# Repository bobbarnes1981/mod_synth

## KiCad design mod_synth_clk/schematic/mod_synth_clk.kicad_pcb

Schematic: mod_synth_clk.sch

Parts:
A1: Arduino_Nano_v3.x; Arduino_Nano
D1: 1N4148; D_DO-35_SOD27_P7.62mm_Horizontal
D2: LED; LED_D5.0mm
J1: Clock; Jack_3.5mm_QingPu_WQP-PJ398SM_Vertical_CircularHoles
J2: Conn_02x08_Odd_Even; IDC-Header_2x08_P2.54mm_Vertical
R1, R2: 1k; R_Axial_DIN0207_L6.3mm_D2.5mm_P10.16mm_Horizontal
RV1: 100k Lin; Potentiometer_Alpha_RD901F-40-00D_Single_Vertical
RV2: 100k Lin; Potentiometer_Alpha_RD901F-40-00D_Single_Vertical_CircularH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

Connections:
+5V: A1.27 (+5V), J2.11, J2.12, RV1.3, RV2.3
GND: A1.29 (GND), D2.1 (K), J1.S, J2.4, J2.6, J2.8, RV1.1, RV2.1
unnamed: A1.16 (D13), D1.2 (A), R2.2
unnamed: A1.19 (A0), RV1.2
unnamed: A1.20 (A1), RV2.2
unnamed: D1.1 (K), R1.1
unnamed: D2.2 (A), R2.1
unnamed: J1.T, R1.2
unnamed: J2.3, J2.5, J2.7

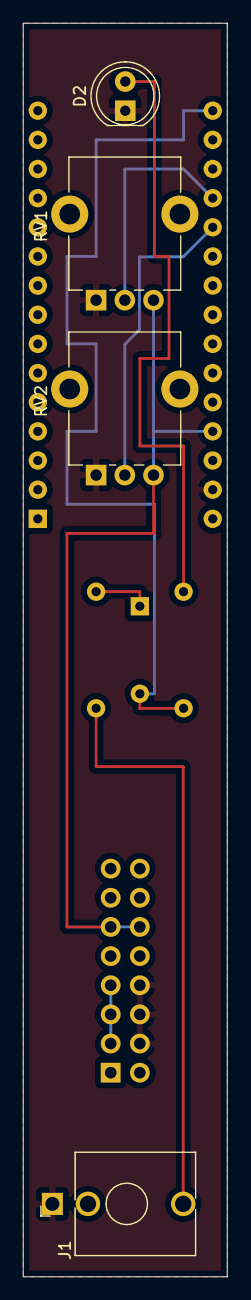
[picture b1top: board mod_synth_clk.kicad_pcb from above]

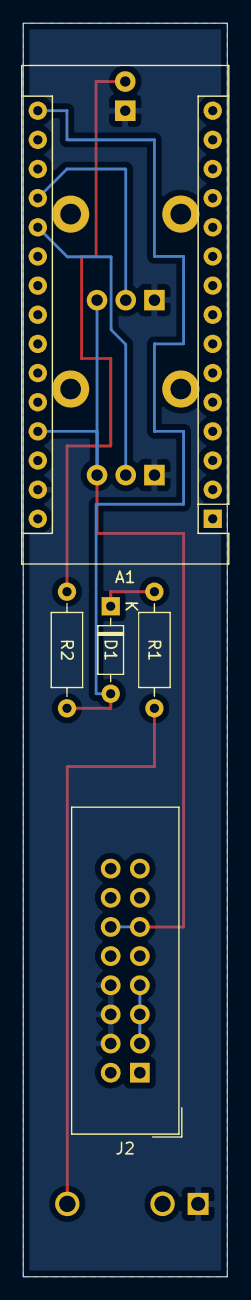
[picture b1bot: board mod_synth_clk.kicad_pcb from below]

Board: 2 copper layers, 17.8 x 109.2 mm, 9 parts (5 on the bottom side), 9 nets.

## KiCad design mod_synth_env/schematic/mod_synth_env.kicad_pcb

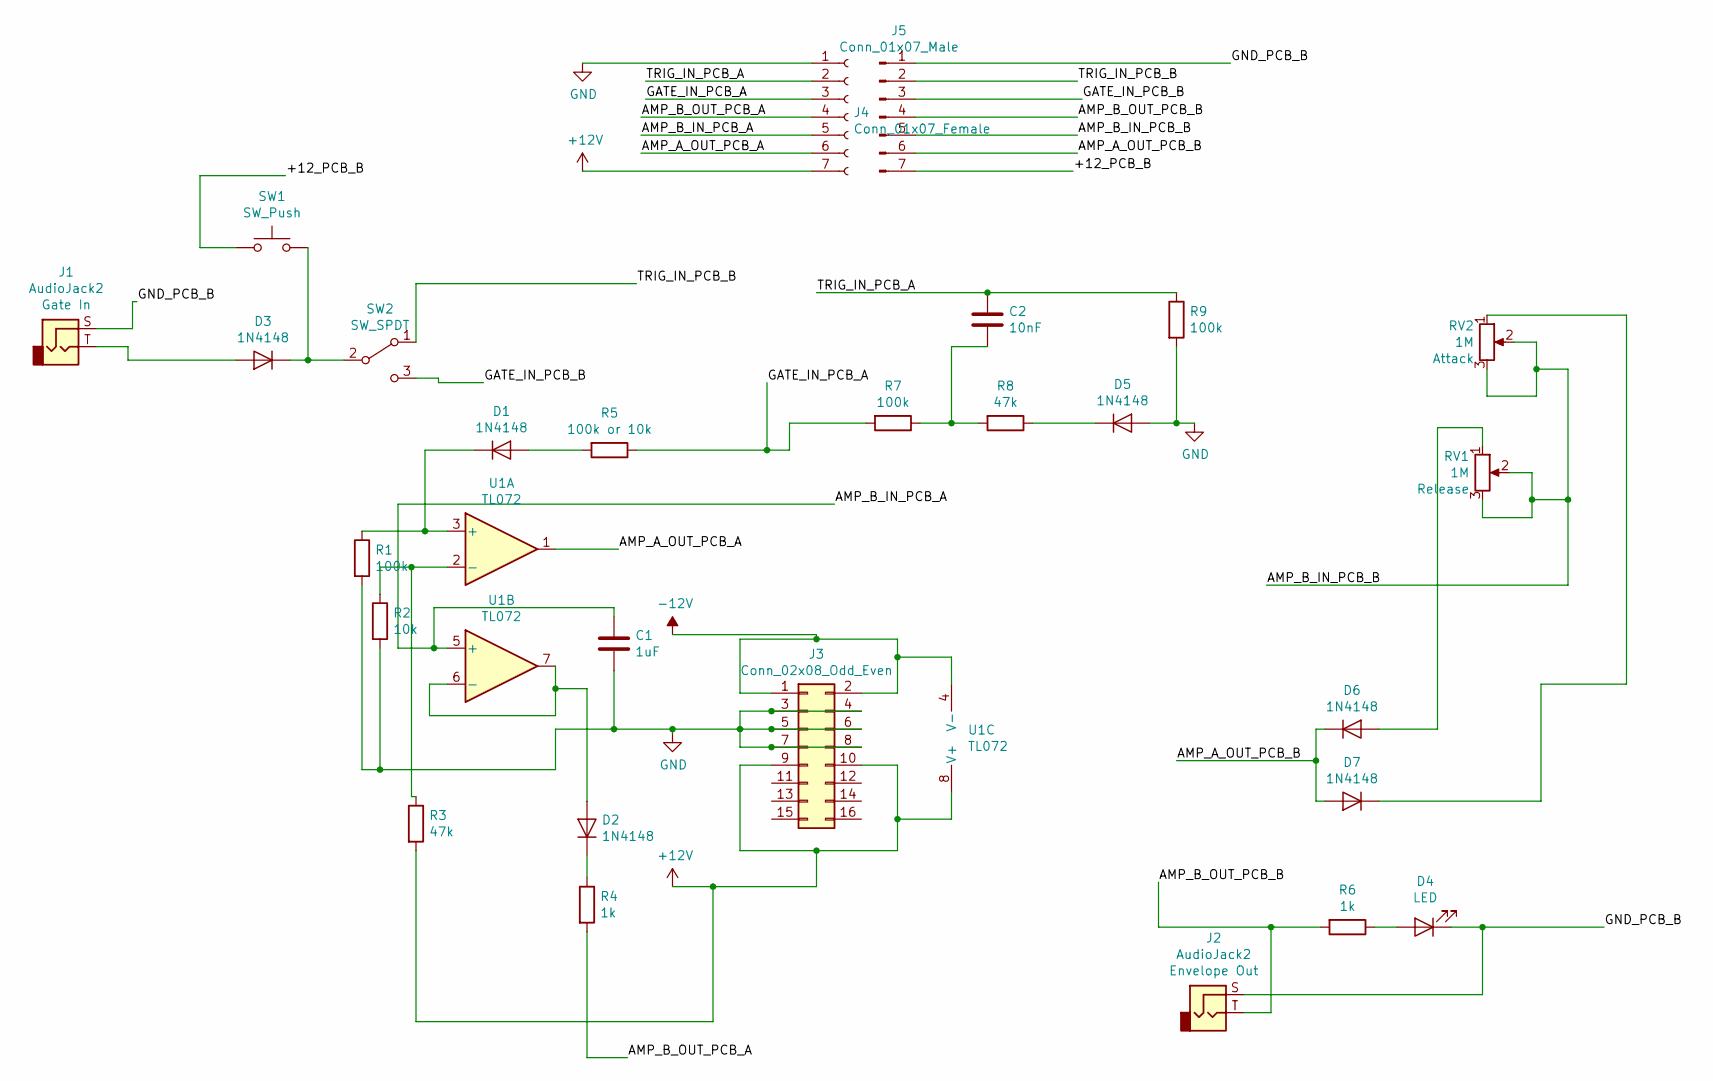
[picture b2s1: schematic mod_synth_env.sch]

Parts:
C1: 1uF; C_Disc_D9.0mm_W2.5mm_P5.00mm
C2: 10nF; C_Disc_D9.0mm_W2.5mm_P5.00mm
D1, D2, D3, D5, D6, D7: 1N4148; D_DO-35_SOD27_P7.62mm_Horizontal
D4: LED; LED_D5.0mm
J1, J2: AudioJack2; Jack_3.5mm_QingPu_WQP-PJ398SM_Vertical_CircularHoles
J3: Conn_02x08_Odd_Even; IDC-Header_2x08_P2.54mm_Vertical
J4: Conn_01x07_Female; PinSocket_1x07_P2.54mm_Vertical
J5: Conn_01x07_Male; PinHeader_1x07_P2.54mm_Vertical
R1, R7, R9: 100k; R_Axial_DIN0207_L6.3mm_D2.5mm_P10.16mm_Horizontal
R2: 10k; R_Axial_DIN0207_L6.3mm_D2.5mm_P10.16mm_Horizontal
R3, R8: 47k; R_Axial_DIN0207_L6.3mm_D2.5mm_P10.16mm_Horizontal
R4, R6: 1k; R_Axial_DIN0207_L6.3mm_D2.5mm_P10.16mm_Horizontal
R5: 100k or 10k; R_Axial_DIN0207_L6.3mm_D2.5mm_P10.16mm_Horizontal
RV1, RV2: 1M; Potentiometer_Alpha_RD901F-40-00D_Single_Vertical_CircularH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
SW1: SW_Push; PinHeader_1x02_P2.54mm_Vertical
SW2: SW_SPDT; SPDT_Switch_Vertical
U1: TL072; DIP-8_W7.62mm_Socket_LongPads

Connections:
+12V: J3.9, J3.10, J4.7, R3.2, U1.8 (V+)
-12V: J3.1, J3.2, U1.4 (V-)
/+12_PCB_B: J5.7, SW1.1
/AMP_A_OUT_PCB_A: J4.6, U1.1
/AMP_A_OUT_PCB_B: D6.1 (K), D7.2 (A), J5.6
/AMP_B_IN_PCB_A: C1.1, J4.5, U1.5 (+)
/AMP_B_IN_PCB_B: J5.5, RV1.2, RV1.3, RV2.2, RV2.3
/AMP_B_OUT_PCB_A: J4.4, R4.2
/AMP_B_OUT_PCB_B: J2.T, J5.4, R6.2
/GATE_IN_PCB_A: J4.3, R5.1, R7.2
/GATE_IN_PCB_B: J5.3, SW2.3 (C)
/GND_PCB_B: D4.1 (K), J1.S, J2.S, J5.1
/TRIG_IN_PCB_A: C2.1, J4.2, R9.1
/TRIG_IN_PCB_B: J5.2, SW2.1 (A)
GND: C1.2, D5.2 (A), J3.3, J3.4, J3.5, J3.6, J3.7, J3.8, J4.1, R1.2, R2.2, R9.2
unnamed: C2.2, R7.1, R8.2
unnamed: D1.1 (K), R1.1, U1.3 (+)
unnamed: D1.2 (A), R5.2
unnamed: D2.1 (K), R4.1
unnamed: D2.2 (A), U1.6 (-), U1.7
unnamed: D3.1 (K), SW1.2, SW2.2 (B)
unnamed: D3.2 (A), J1.T
unnamed: D4.2 (A), R6.1
unnamed: D5.1 (K), R8.1
unnamed: D6.2 (A), RV1.1
unnamed: D7.1 (K), RV2.1
unnamed: R2.1, R3.1, U1.2 (-)

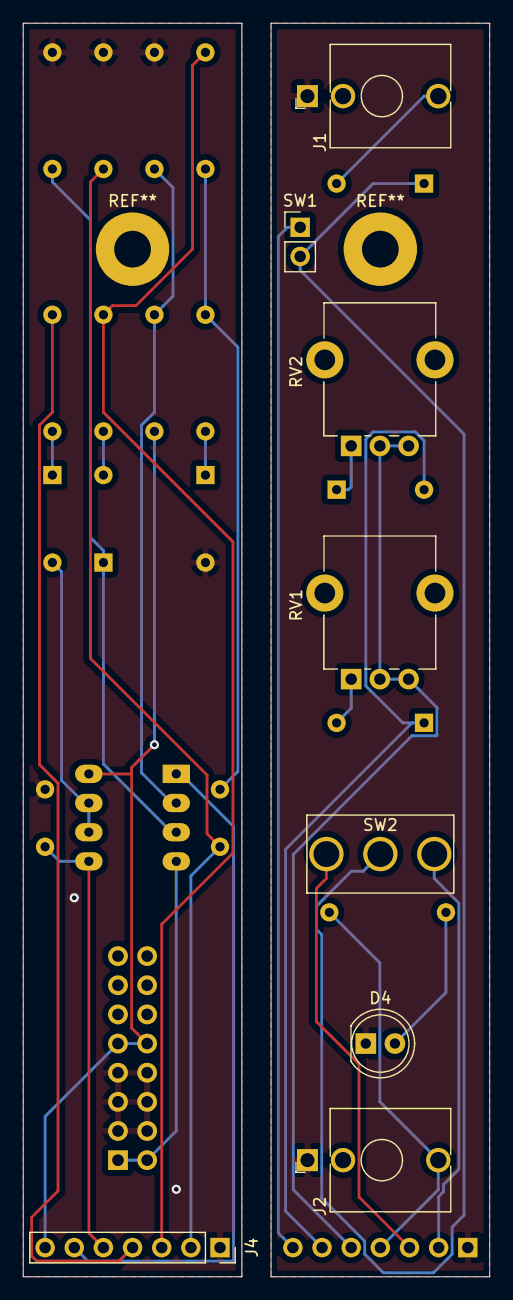
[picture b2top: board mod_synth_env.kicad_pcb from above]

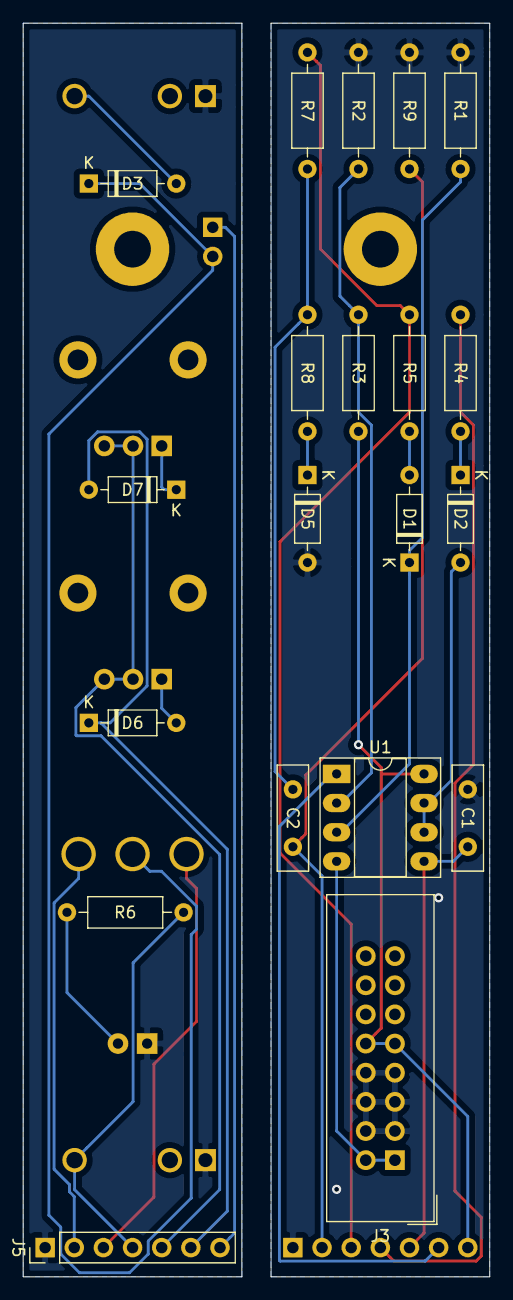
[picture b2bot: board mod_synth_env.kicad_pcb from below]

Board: 2 copper layers, 40.6 x 109.2 mm, 28 parts (20 on the bottom side), 27 nets.

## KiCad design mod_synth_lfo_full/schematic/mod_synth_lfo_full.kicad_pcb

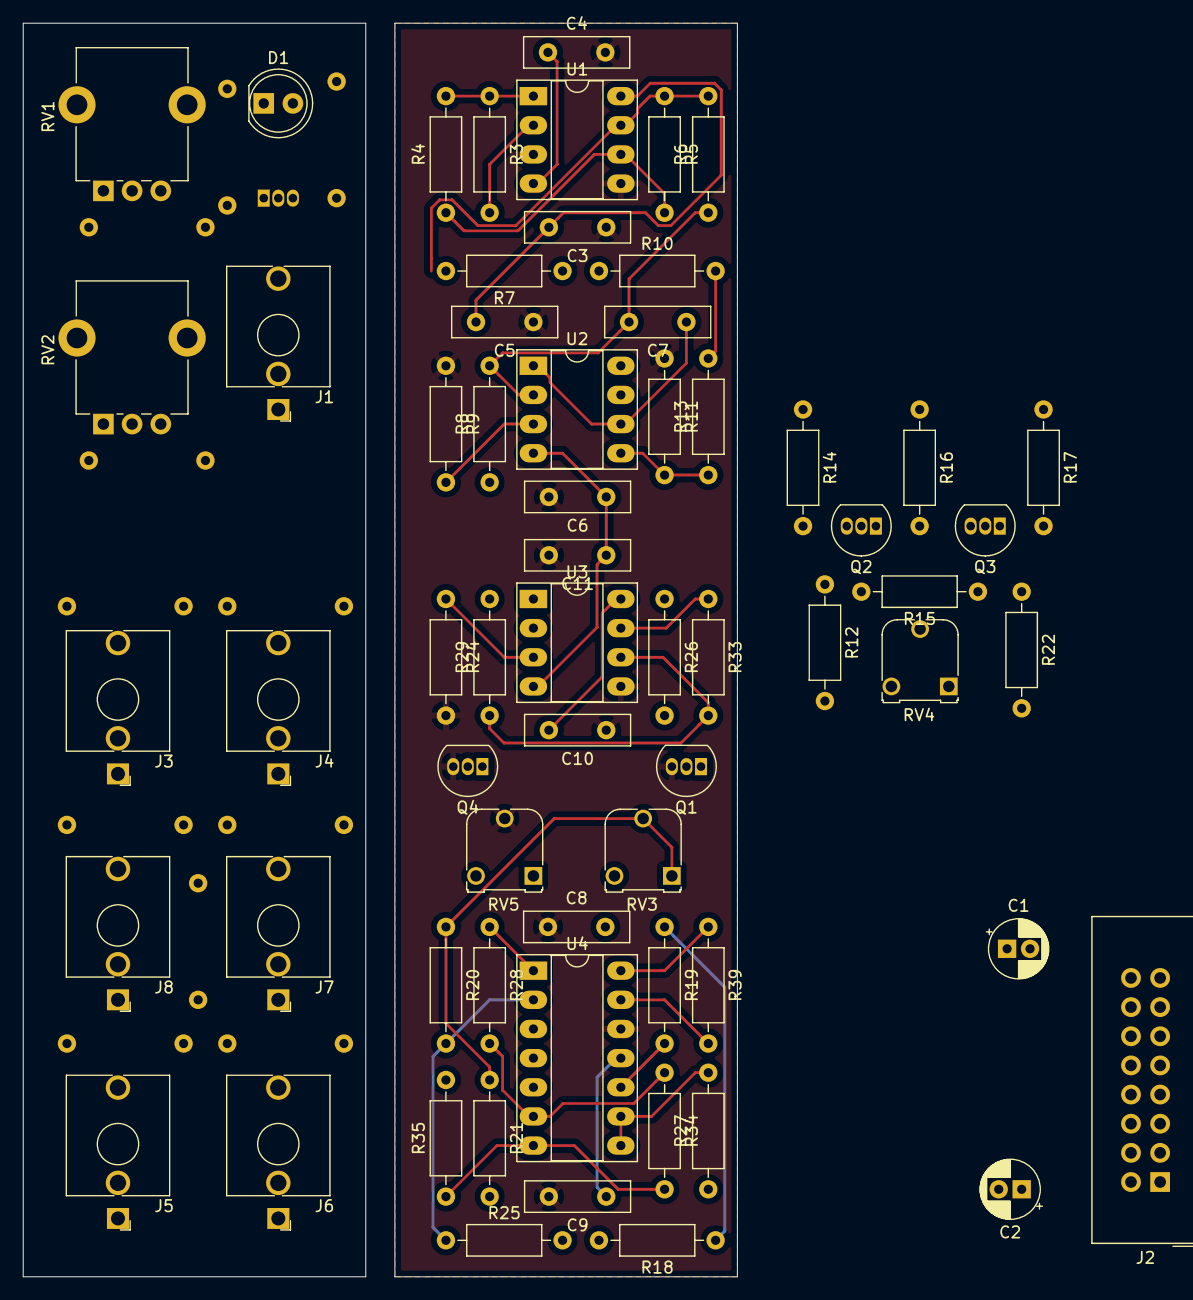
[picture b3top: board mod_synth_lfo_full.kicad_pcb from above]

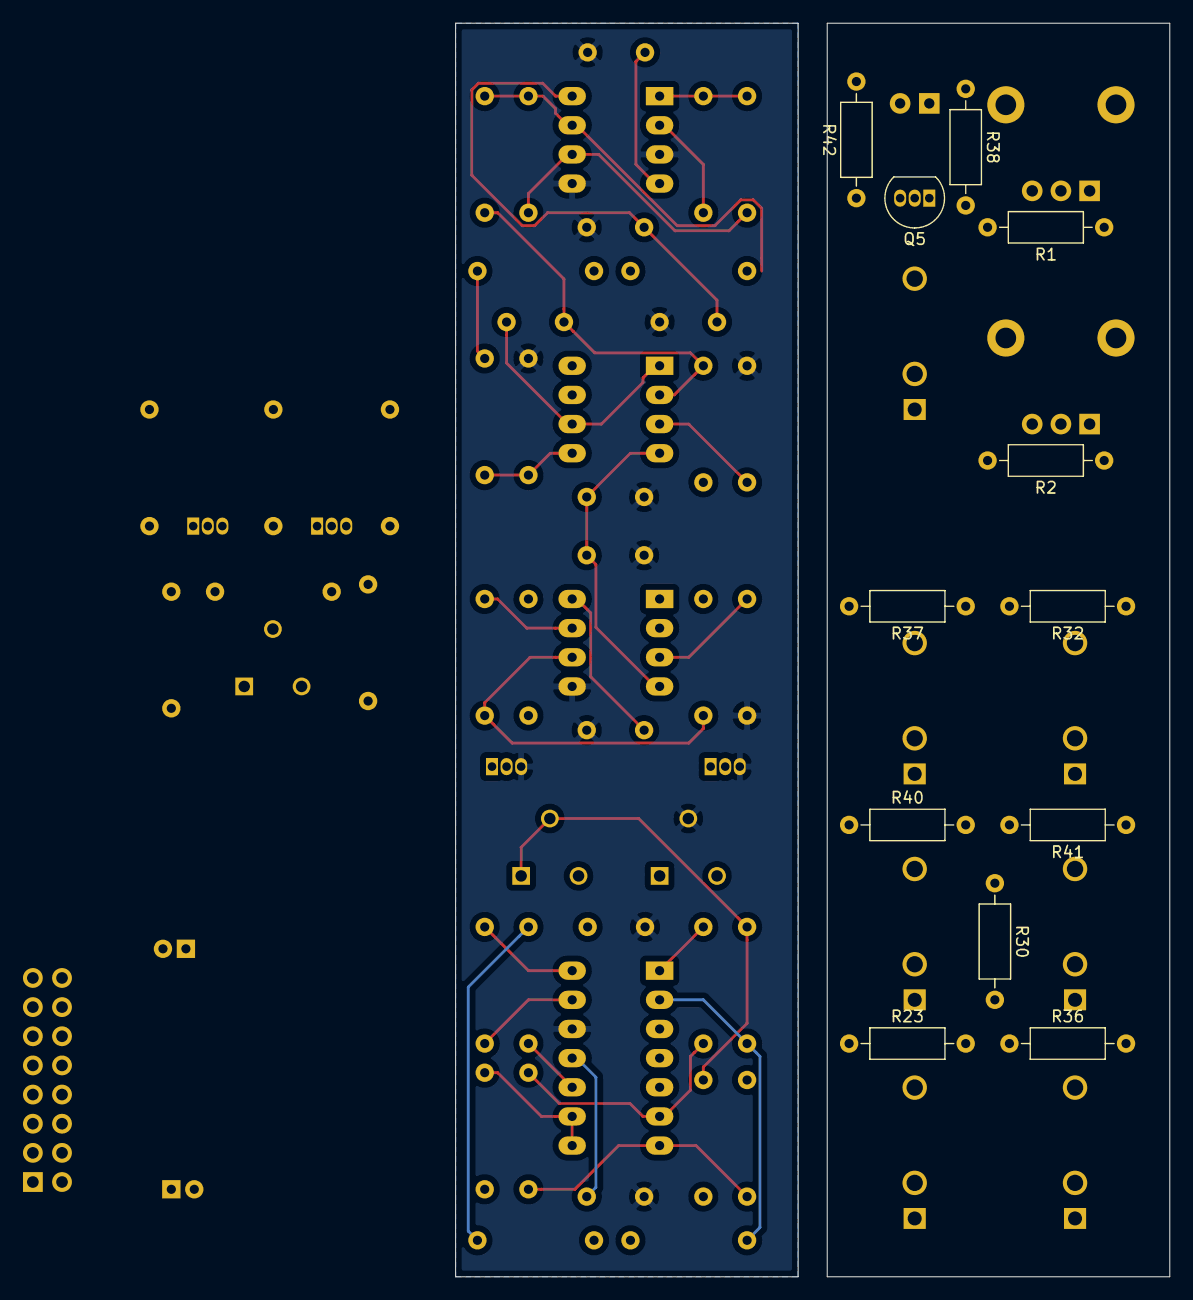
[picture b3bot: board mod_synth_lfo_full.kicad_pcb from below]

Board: 2 copper layers, 62.2 x 109.2 mm, 75 parts (12 on the bottom side), 47 nets.

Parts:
C1, C2: 10uf; CP_Radial_D5.0mm_P2.00mm
C3, C4, C5, C6, C7, C8, C9, C10, C11: 100nf; C_Disc_D9.0mm_W2.5mm_P5.00mm
D1: LED; LED_D5.0mm
J1: CV; Jack_3.5mm_QingPu_WQP-PJ398SM_Vertical_CircularHoles
J2: Conn_02x08_Odd_Even; IDC-Header_2x08_P2.54mm_Vertical
J3: SIN; Jack_3.5mm_QingPu_WQP-PJ398SM_Vertical_CircularHoles
J4: COS; Jack_3.5mm_QingPu_WQP-PJ398SM_Vertical_CircularHoles
J5: TRI; Jack_3.5mm_QingPu_WQP-PJ398SM_Vertical_CircularHoles
J6: SQR; Jack_3.5mm_QingPu_WQP-PJ398SM_Vertical_CircularHoles
J7: RAMP UP; Jack_3.5mm_QingPu_WQP-PJ398SM_Vertical_CircularHoles
J8: RAMP DOWN; Jack_3.5mm_QingPu_WQP-PJ398SM_Vertical_CircularHoles
Q1, Q2, Q3, Q4, Q5: BC550; TO-92_Inline
R1, R2, R3, R4, R5, R6, R19, R20, R21, R23, R25, R30: 100k; R_Axial_DIN0207_L6.3mm_D2.5mm_P10.16mm_Horizontal
R7, R8, R9, R11, R13: 47k; R_Axial_DIN0207_L6.3mm_D2.5mm_P10.16mm_Horizontal
R10, R14, R17, R18, R29, R33, R34, R35, R38, R39: 10k; R_Axial_DIN0207_L6.3mm_D2.5mm_P10.16mm_Horizontal
R12, R22: 470; R_Axial_DIN0207_L6.3mm_D2.5mm_P10.16mm_Horizontal
R15: 220; R_Axial_DIN0207_L6.3mm_D2.5mm_P10.16mm_Horizontal
R16: 68k; R_Axial_DIN0207_L6.3mm_D2.5mm_P10.16mm_Horizontal
R24, R26: 33k; R_Axial_DIN0207_L6.3mm_D2.5mm_P10.16mm_Horizontal
R27: 50k; R_Axial_DIN0207_L6.3mm_D2.5mm_P10.16mm_Horizontal
R28: 20k; R_Axial_DIN0207_L6.3mm_D2.5mm_P10.16mm_Horizontal
R32, R36, R37, R40, R41, R42: 1k; R_Axial_DIN0207_L6.3mm_D2.5mm_P10.16mm_Horizontal
RV1: SPEED; Potentiometer_Alpha_RD901F-40-00D_Single_Vertical_CircularH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
RV2: CV AMOUNT; Potentiometer_Alpha_RD901F-40-00D_Single_Vertical_CircularH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
RV3: 100k; Potentiometer_Runtron_RM-065_Vertical
RV4: 50k; Potentiometer_Runtron_RM-065_Vertical
RV5: 20k; Potentiometer_Runtron_RM-065_Vertical
U1, U2, U3: TL072; DIP-8_W7.62mm_Socket_LongPads
U4: TL074; DIP-14_W7.62mm_Socket_LongPads

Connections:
+12V: C1.1, C3.2, C5.2, C8.2, C10.2, D1.2, J2.9, J2.10, R14.1, R17.1, RV1.1, U1.8, U2.8, U3.8, U4.4
-12V: C2.2, C4.1, C6.1, C9.1, C11.1, J2.1, J2.2, R16.1, U1.4, U2.4, U3.4, U4.11
GND: C1.2, C2.1, C3.1, C4.2, C5.1, C6.2, C8.1, C9.2, C10.1, C11.2, J1.S, J2.3, J2.4, J2.5, J2.6, J2.7, J2.8, J3.S, J4.S, J5.S, J6.S, J7.S, J8.S, Q1.3, Q4.3, R9.1, R11.1, R12.2, R22.2, R24.2, R30.2, R42.2, RV1.3, RV2.3, RV5.2, U1.3, U1.5, U3.5, U4.12
unnamed: C7.1, R20.1, R21.1, R36.1, R38.1, RV3.1, RV3.2, U2.1, U2.6
unnamed: C7.2, R6.1, R8.2, U2.2
unnamed: D1.1, Q5.1
unnamed: J1.T, RV2.1
unnamed: J3.T, R32.1
unnamed: J4.T, R37.1
unnamed: J5.T, R36.2
unnamed: J6.T, R23.2, R30.1
unnamed: J7.T, R40.2
unnamed: J8.T, R41.1
unnamed: Q1.1, R8.1
unnamed: Q1.2, R10.1
unnamed: Q2.1, R14.2, R26.2, U3.2
unnamed: Q2.2, R12.1, RV3.3
unnamed: Q2.3, R15.2, RV4.3
unnamed: Q3.1, R17.2, R24.1, U3.3
unnamed: Q3.2, R22.1
unnamed: Q3.3, R15.1, RV4.1
unnamed: Q4.1, R21.2, U4.3
unnamed: Q4.2, R18.2
unnamed: Q5.2, R38.2
unnamed: Q5.3, R42.1
unnamed: R1.1, R2.1, R3.2, U1.2
unnamed: R1.2, RV1.2
unnamed: R2.2, RV2.2
unnamed: R3.1, R4.2, U1.1
unnamed: R4.1, R5.2, U1.6
unnamed: R5.1, R6.2, R7.2, U1.7
unnamed: R7.1, R9.2, U2.3
unnamed: R10.2, R13.2, R18.1, R19.1, R23.1, U2.7
unnamed: R11.2, R13.1, U2.5
unnamed: R16.2, RV4.2
unnamed: R19.2, U4.10
unnamed: R20.2, R25.1, U4.2
unnamed: R25.2, R28.1, U4.1
unnamed: R26.1, R29.2, R32.2, U3.1
unnamed: R27.1, RV5.1, U4.5
unnamed: R27.2, U4.8, U4.9
unnamed: R28.2, R34.1, U4.6
unnamed: R29.1, R33.2, U3.6
unnamed: R33.1, R37.2, U3.7
unnamed: R34.2, R35.1, R40.1, U4.7
unnamed: R35.2, R39.2, U4.13
unnamed: R39.1, R41.2, U4.14

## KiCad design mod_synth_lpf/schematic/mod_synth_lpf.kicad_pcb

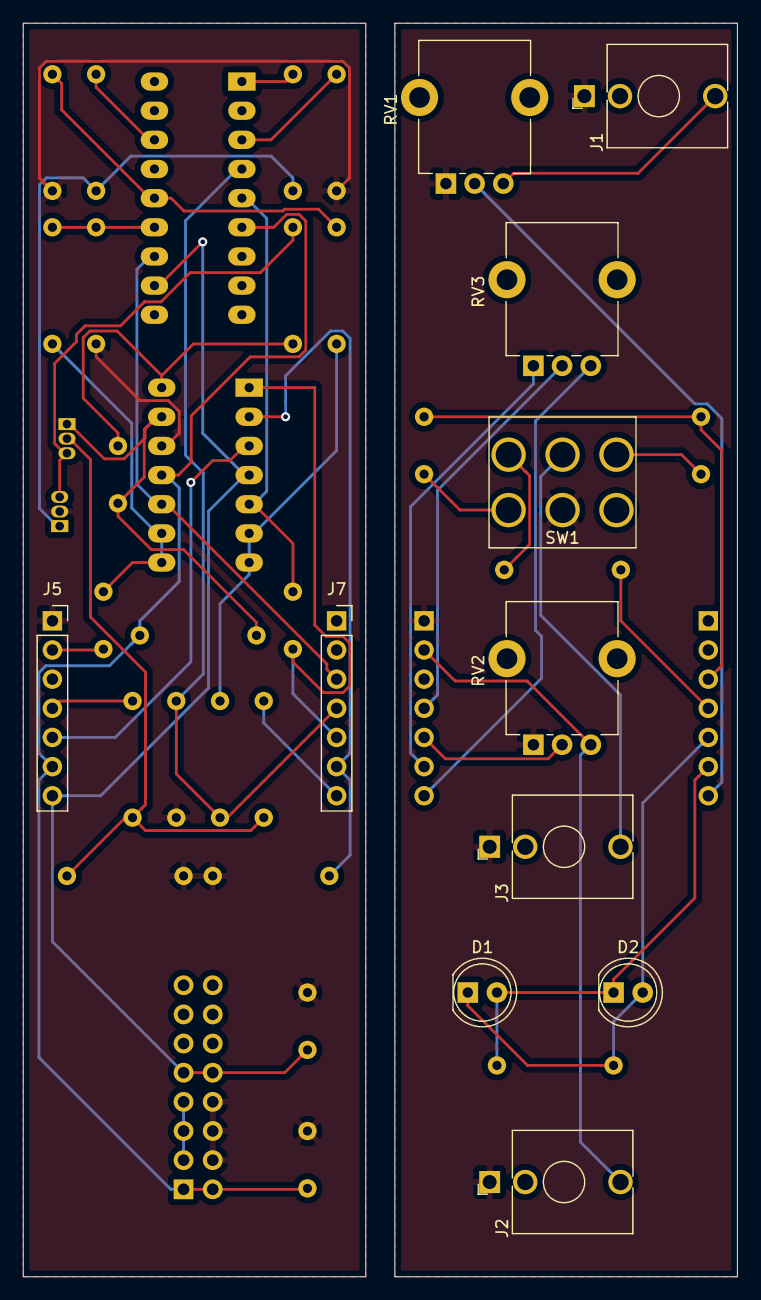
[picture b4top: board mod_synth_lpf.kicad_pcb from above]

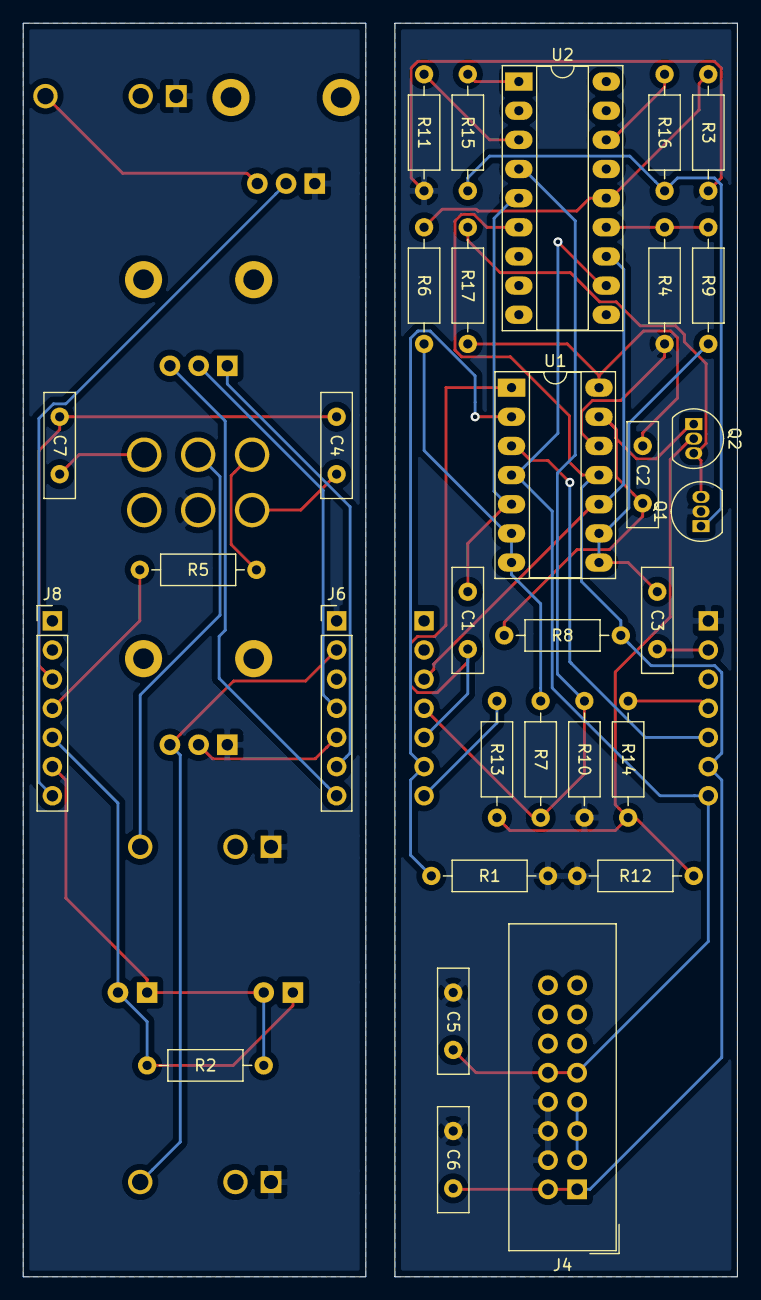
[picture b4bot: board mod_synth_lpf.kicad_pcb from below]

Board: 2 copper layers, 62.2 x 109.2 mm, 42 parts (31 on the bottom side), 41 nets.

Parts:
C1, C4, C7: 1nf; C_Disc_D9.0mm_W2.5mm_P5.00mm
C2: 4.7nf; C_Disc_D9.0mm_W2.5mm_P5.00mm
C3: 470nf; C_Disc_D9.0mm_W2.5mm_P5.00mm
C5, C6: 100nf; C_Disc_D9.0mm_W2.5mm_P5.00mm
D1, D2: LED; LED_D5.0mm
J1, J2, J3: AudioJack2; Jack_3.5mm_QingPu_WQP-PJ398SM_Vertical_CircularHoles
J4: Conn_02x08_Odd_Even; IDC-Header_2x08_P2.54mm_Vertical
J5, J7: Conn_01x07_Female; PinSocket_1x07_P2.54mm_Vertical
J6, J8: Conn_01x07_Male; PinHeader_1x07_P2.54mm_Vertical
Q1, Q2: BC558; TO-92_Inline
R1, R12: 1k8; R_Axial_DIN0207_L6.3mm_D2.5mm_P10.16mm_Horizontal
R2, R5, R6, R7, R9, R15, R16: 10k; R_Axial_DIN0207_L6.3mm_D2.5mm_P10.16mm_Horizontal
R3, R4, R10, R11: 220; R_Axial_DIN0207_L6.3mm_D2.5mm_P10.16mm_Horizontal
R8: 470k; R_Axial_DIN0207_L6.3mm_D2.5mm_P10.16mm_Horizontal
R13, R14: 100k; R_Axial_DIN0207_L6.3mm_D2.5mm_P10.16mm_Horizontal
R17: 4k7; R_Axial_DIN0207_L6.3mm_D2.5mm_P10.16mm_Horizontal
RV1, RV2: 100k Linear; Potentiometer_Alpha_RD901F-40-00D_Single_Vertical_CircularH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
RV3: 4.7k Linear; Potentiometer_Alpha_RD901F-40-00D_Single_Vertical_CircularH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
SW1: SW_DPDT_x2; DPDT_Switch_Vertical
U1: TL074; DIP-14_W7.62mm_Socket_LongPads
U2: LM13700; DIP-18_W7.62mm_Socket_LongPads

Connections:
+12V: C5.2, J4.9, J4.10, J5.7, U1.4, U2.11
-12V: C6.2, J4.1, J4.2, J5.6, R8.2, U1.11, U2.6
/+12_PCB_B: J6.7, RV3.3
/-12_PCB_B: J6.6, RV3.1
/AUDIO_OUT_PCB_A: C3.2, J5.2
/AUDIO_OUT_PCB_B: J2.T, J6.2, RV2.3
/CUT_OFF_PCB_A: J5.4, R14.2
/CUT_OFF_PCB_B: J6.4, RV3.2
/CV_PCB_A: J7.7, R13.1
/CV_PCB_B: J8.7, RV1.2
/GND_PCB_B: J1.S, J2.S, J3.S, J6.1, RV1.1, RV2.1, SW1.2
/INDICATOR_1_PCB_A: J7.6, R1.1, U1.2
/INDICATOR_1_PCB_B: D1.2, D2.1, J8.6, R2.2
/INDICATOR_2_PCB_A: C1.2, J7.5, U1.1
/INDICATOR_2_PCB_B: D1.1, D2.2, J8.5, R2.1
/RESONANCE_PCB_A: J5.5, U1.3
/RESONANCE_PCB_B: J6.5, RV2.2
/SWA_PCB_A: J7.3, U1.10, U2.12
/SWA_PCB_B: C4.1, C7.1, J8.3
/SWB_PCB_A: J7.4, R7.1, R10.1, U2.4
/SWB_PCB_B: J8.4, R5.1
GND: C5.1, C6.1, J4.4, J4.6, J4.8, J5.1, Q1.2, R1.2, R3.1, R4.1, R10.2, R11.2, R12.2, U1.12
unnamed: C1.1, U1.5, U2.5
unnamed: C2.1, R17.2, U1.14
unnamed: C2.2, Q2.1, R8.1, U1.13
unnamed: C3.1, R9.2, U1.8, U1.9
unnamed: C4.2, SW1.1
unnamed: C7.2, SW1.6
unnamed: J1.T, RV1.3
unnamed: J3.T, SW1.5
unnamed: J4.3, J4.5, J4.7
unnamed: Q1.1, R15.2, R16.1
unnamed: Q1.3, Q2.3, R17.1
unnamed: Q2.2, R12.1, R13.2, R14.1
unnamed: R3.2, R6.2, U2.14
unnamed: R4.2, R9.1, U2.13
unnamed: R5.2, SW1.4
unnamed: R6.1, R7.2, U1.6, U1.7
unnamed: R11.1, U2.3
unnamed: R15.1, U2.1
unnamed: R16.2, U2.16

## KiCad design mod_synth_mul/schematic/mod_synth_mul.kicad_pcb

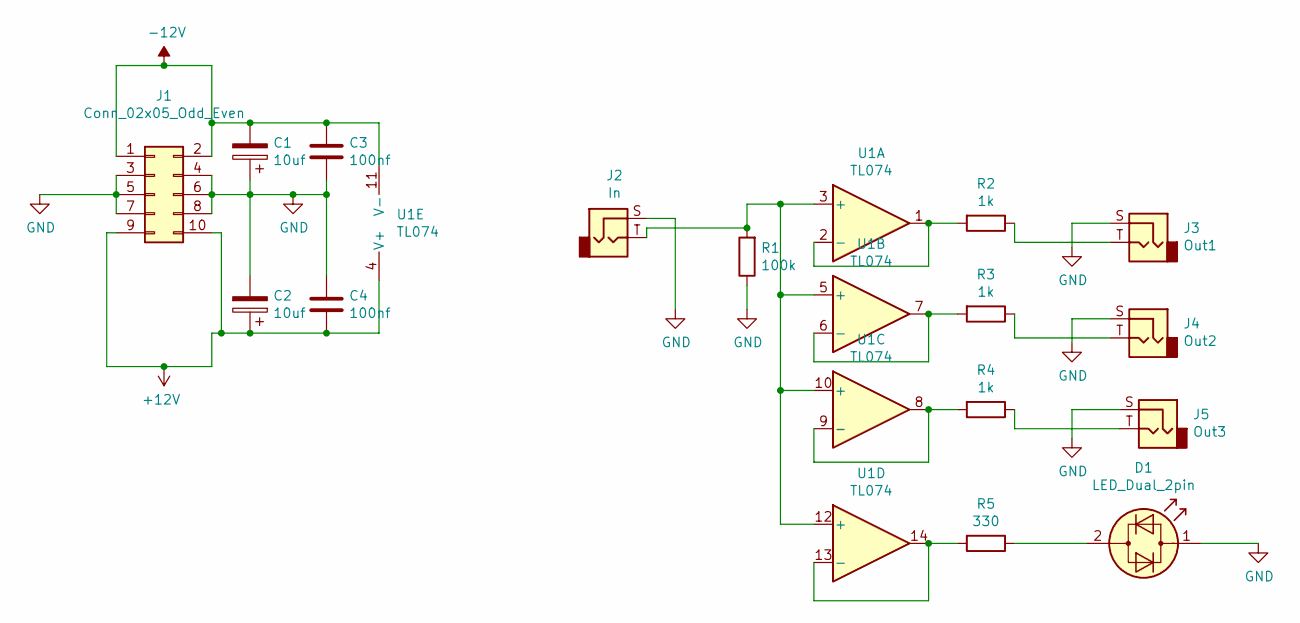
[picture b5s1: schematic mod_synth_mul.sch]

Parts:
C1, C2: 10uf; CP_Radial_D5.0mm_P2.00mm
C3, C4: 100nf; C_Disc_D9.0mm_W2.5mm_P5.00mm
D1: LED_Dual_2pin; LED_D5.0mm
J1: Conn_02x05_Odd_Even; IDC-Header_2x05_P2.54mm_Vertical
J2: In; Jack_3.5mm_QingPu_WQP-PJ398SM_Vertical_CircularHoles
J3: Out1; Jack_3.5mm_QingPu_WQP-PJ398SM_Vertical_CircularHoles
J4: Out2; Jack_3.5mm_QingPu_WQP-PJ398SM_Vertical_CircularHoles
J5: Out3; Jack_3.5mm_QingPu_WQP-PJ398SM_Vertical_CircularHoles
R1: 100k; R_Axial_DIN0207_L6.3mm_D2.5mm_P10.16mm_Horizontal
R2, R3, R4: 1k; R_Axial_DIN0207_L6.3mm_D2.5mm_P10.16mm_Horizontal
R5: 330; R_Axial_DIN0207_L6.3mm_D2.5mm_P10.16mm_Horizontal
U1: TL074; DIP-14_W7.62mm_Socket_LongPads

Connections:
+12V: C2.1, C4.2, J1.9, J1.10, U1.4 (V+)
-12V: C1.2, C3.1, J1.1, J1.2, U1.11 (V-)
GND: C1.1, C2.2, C3.2, C4.1, D1.1 (KA), J1.3, J1.4, J1.5, J1.6, J1.7, J1.8, J2.S, J3.S, J4.S, J5.S, R1.1
unnamed: D1.2 (AK), R5.1
unnamed: J2.T, R1.2, U1.3 (+), U1.5 (+), U1.10 (+), U1.12 (+)
unnamed: J3.T, R2.1
unnamed: J4.T, R3.1
unnamed: J5.T, R4.1
unnamed: R2.2, U1.1, U1.2 (-)
unnamed: R3.2, U1.6 (-), U1.7
unnamed: R4.2, U1.8, U1.9 (-)
unnamed: R5.2, U1.13 (-), U1.14

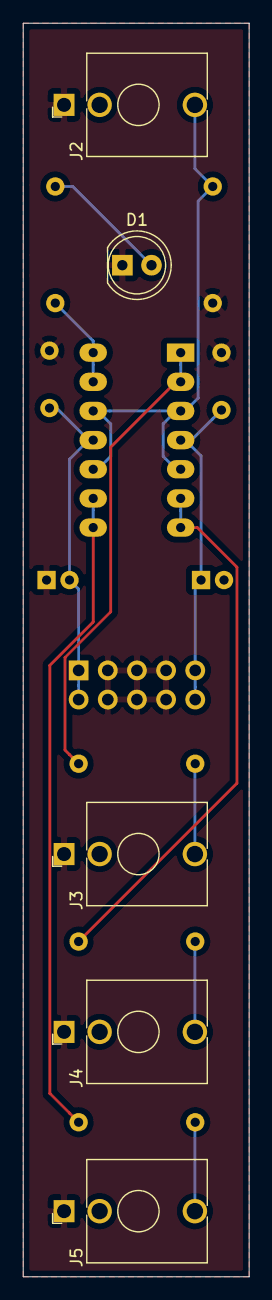
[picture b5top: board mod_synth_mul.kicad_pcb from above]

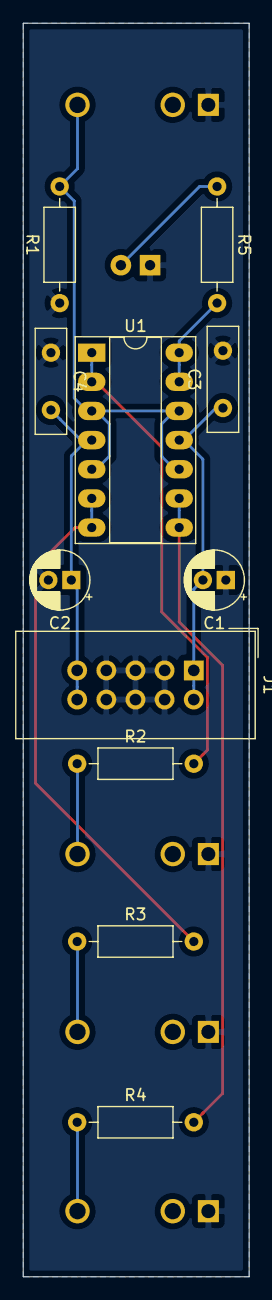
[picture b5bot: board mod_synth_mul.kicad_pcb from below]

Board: 2 copper layers, 19.7 x 109.2 mm, 16 parts (11 on the bottom side), 12 nets.

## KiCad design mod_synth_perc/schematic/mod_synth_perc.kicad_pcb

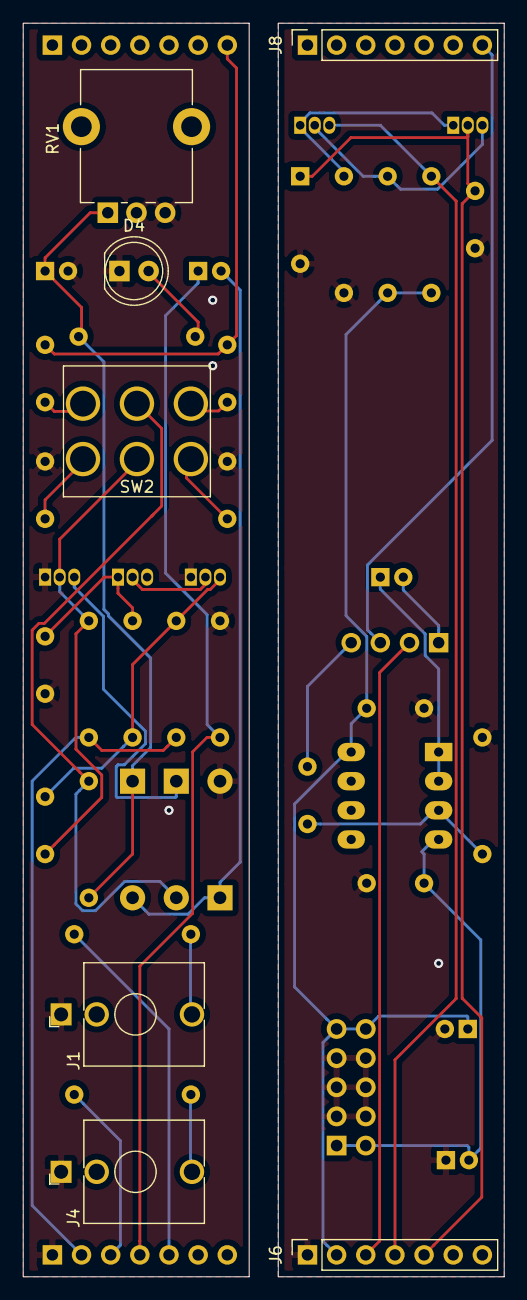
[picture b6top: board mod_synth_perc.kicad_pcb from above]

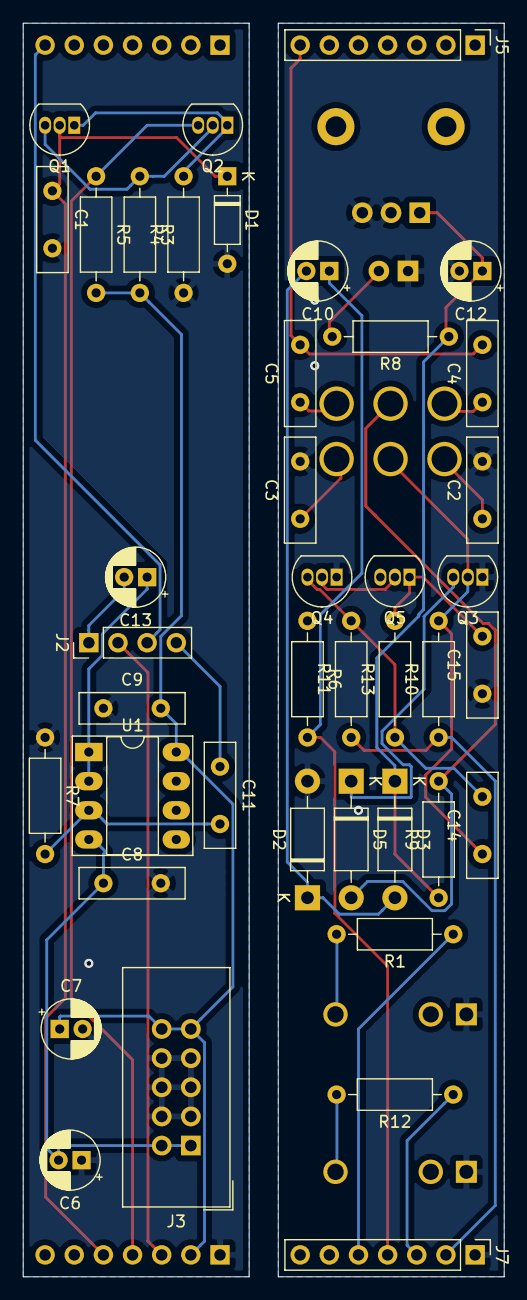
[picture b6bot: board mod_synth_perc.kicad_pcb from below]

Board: 2 copper layers, 41.9 x 109.2 mm, 48 parts (41 on the bottom side), 34 nets.

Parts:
C1: 100nf to 1uf; C_Disc_D9.0mm_W2.5mm_P5.00mm
C2: 0.001uf (Hihat); C_Disc_D9.0mm_W2.5mm_P5.00mm
C3: 0.1uf (Snare); C_Disc_D9.0mm_W2.5mm_P5.00mm
C4: 680pf (Hihat); C_Disc_D9.0mm_W2.5mm_P5.00mm
C5: 0.005uf (Snare); C_Disc_D9.0mm_W2.5mm_P5.00mm
C6, C7, C10, C12, C13: 10uf; CP_Radial_D5.0mm_P2.00mm
C8, C9: 100nf; C_Disc_D9.0mm_W2.5mm_P5.00mm
C11, C14, C15: 0.1uf; C_Disc_D9.0mm_W2.5mm_P5.00mm
D1: 1N4148; D_DO-35_SOD27_P7.62mm_Horizontal
D2, D3, D5: 1N4001; D_DO-41_SOD81_P10.16mm_Horizontal
D4: LED; LED_D5.0mm
J1: Trigger; Jack_3.5mm_QingPu_WQP-PJ398SM_Vertical_CircularHoles
J2: Conn_01x04_Male; PinHeader_1x04_P2.54mm_Vertical
J3: Conn_02x05_Odd_Even; IDC-Header_2x05_P2.54mm_Vertical
J4: Out; Jack_3.5mm_QingPu_WQP-PJ398SM_Vertical_CircularHoles
J5, J7: Conn_01x07_Male; PinHeader_1x07_P2.54mm_Vertical
J6, J8: Conn_01x07_Female; PinSocket_1x07_P2.54mm_Vertical
Q1, Q2, Q3, Q4, Q5: 2N3904; TO-92_Inline
R1: 100k; R_Axial_DIN0207_L6.3mm_D2.5mm_P10.16mm_Horizontal
R3, R13: 47k; R_Axial_DIN0207_L6.3mm_D2.5mm_P10.16mm_Horizontal
R4: 220; R_Axial_DIN0207_L6.3mm_D2.5mm_P10.16mm_Horizontal
R5, R11: 4k7; R_Axial_DIN0207_L6.3mm_D2.5mm_P10.16mm_Horizontal
R6: 4k7 (OPTIONAL); R_Axial_DIN0207_L6.3mm_D2.5mm_P10.16mm_Horizontal
R7, R10: 1m; R_Axial_DIN0207_L6.3mm_D2.5mm_P10.16mm_Horizontal
R8, R12: 1k; R_Axial_DIN0207_L6.3mm_D2.5mm_P10.16mm_Horizontal
R9: 33k; R_Axial_DIN0207_L6.3mm_D2.5mm_P10.16mm_Horizontal
RV1: 1m (Decay); Potentiometer_Alpha_RD901F-40-00D_Single_Vertical_CircularH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
SW2: SW_DPDT_x2; DPDT_Switch_Vertical
U1: TL072; DIP-8_W7.62mm_Socket_LongPads

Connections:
+12V: C7.1, C9.2, J3.9, J3.10, J6.2, R3.2, R5.2, U1.8
-12V: C6.2, C8.1, J3.1, J3.2, U1.4
/+12_PCB_B: J7.2, R10.1, R11.1
/Buffer_In: C11.1, J2.4
/Buffer_Out: C13.2, J2.1
/C1_Hihat: C2.1, SW2.1
/C1_IN: C14.1, Q3.2, R10.2, SW2.2
/C1_Snare: C3.1, SW2.3
/C2_Hihat: C4.1, SW2.4
/C2_IN: D5.2, R9.2, SW2.5
/C2_Snare: C5.1, SW2.6
/GND_PCB_B: C2.2, C3.2, C12.2, C15.1, D2.2, D4.1, J1.S, J4.S, J7.1, Q3.1, Q4.1, R6.1, RV1.2, RV1.3
/IN_PCB_A: C1.1, D1.1, J6.5, Q1.2
/IN_PCB_B: J7.5, R1.1
/Main_Out_PCB_A: J2.2, J6.3
/Main_Out_PCB_B: J7.3, R12.1
/Noise_Out_PCB_A: J2.3, J8.7
/Noise_Out_PCB_B: C4.2, C5.2, J5.7
/Trigger_PCB_A: J6.4, Q2.3, R5.1
/Trigger_PCB_B: C10.1, J7.4, R6.2
GND: C1.2, C6.1, C7.2, C8.2, C9.1, D1.2, J3.3, J3.4, J3.5, J3.6, J3.7, J3.8, J6.1, R4.1, R7.1
unnamed: C10.2, D2.1, D3.2
unnamed: C11.2, R7.2, U1.3
unnamed: C12.1, D3.1, R8.1, R9.1, RV1.1
unnamed: C13.1, U1.1, U1.2
unnamed: C14.2, Q4.3, R11.2, R13.1
unnamed: C15.2, Q5.1, R13.2
unnamed: D4.2, R8.2
unnamed: D5.1, Q3.3
unnamed: J1.T, R1.2
unnamed: J4.T, R12.2
unnamed: Q1.1, Q2.1, R4.2
unnamed: Q1.3, Q2.2, R3.1
unnamed: Q4.2, Q5.2

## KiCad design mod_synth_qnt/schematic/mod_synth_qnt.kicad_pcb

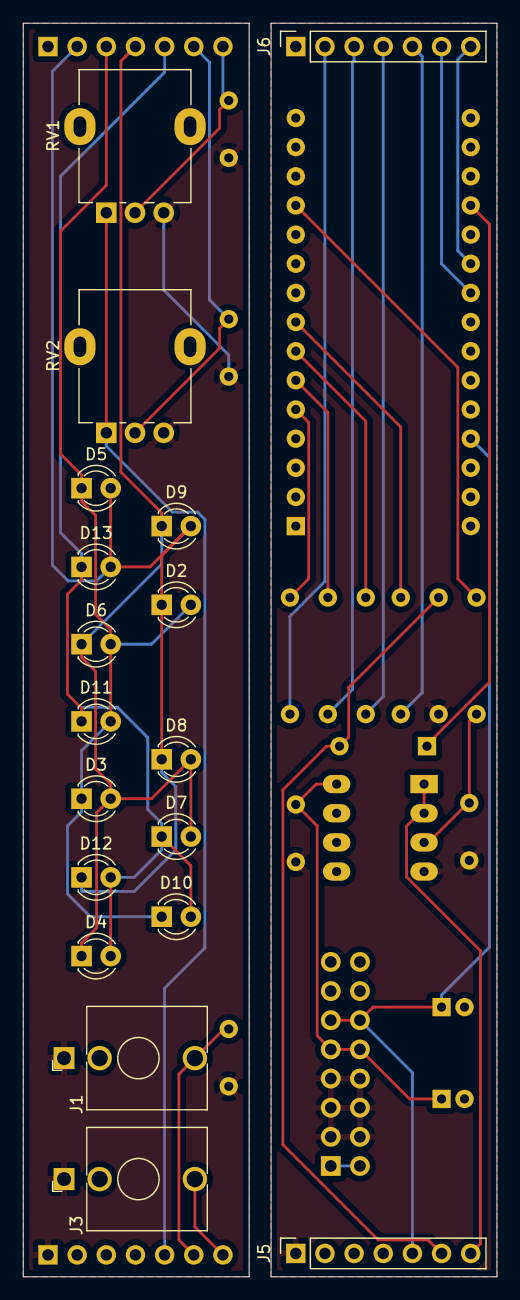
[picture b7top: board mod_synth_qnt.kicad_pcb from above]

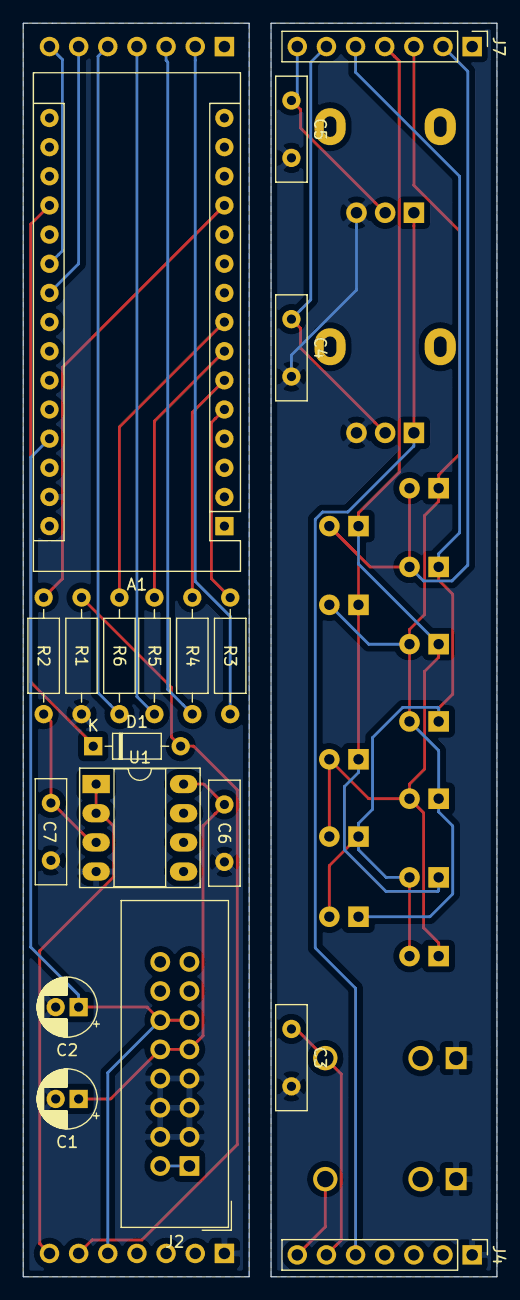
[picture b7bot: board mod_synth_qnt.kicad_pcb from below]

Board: 2 copper layers, 41.3 x 109.2 mm, 37 parts (19 on the bottom side), 29 nets.

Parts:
A1: Arduino_Nano_v3.x; Arduino_Nano
C1, C2: 10uf; CP_Radial_D5.0mm_P2.00mm
C3, C4, C5, C6, C7: 100nf; C_Disc_D9.0mm_W2.5mm_P5.00mm
D1: 1N4148; D_DO-35_SOD27_P7.62mm_Horizontal
D2: LED 3; LED_D3.0mm
D3: LED 7; LED_D3.0mm
D4: LED 11; LED_D3.0mm
D5: LED 0; LED_D3.0mm
D6: LED 4; LED_D3.0mm
D7: LED 8; LED_D3.0mm
D8: LED 6; LED_D3.0mm
D9: LED 1; LED_D3.0mm
D10: LED 10; LED_D3.0mm
D11: LED 5; LED_D3.0mm
D12: LED 9; LED_D3.0mm
D13: LED 2; LED_D3.0mm
J1: CV IN; Jack_3.5mm_QingPu_WQP-PJ398SM_Vertical_CircularHoles
J2: Conn_02x08_Odd_Even; IDC-Header_2x08_P2.54mm_Vertical
J3: QUANTIZE OUT; Jack_3.5mm_QingPu_WQP-PJ398SM_Vertical_CircularHoles
J4, J7: Conn_01x07_Male; PinHeader_1x07_P2.54mm_Vertical
J5, J6: Conn_01x07_Female; PinSocket_1x07_P2.54mm_Vertical
R1, R2: 10k; R_Axial_DIN0207_L6.3mm_D2.5mm_P10.16mm_Horizontal
R3, R4, R5, R6: 330; R_Axial_DIN0207_L6.3mm_D2.5mm_P10.16mm_Horizontal
RV1: 100k Note; Potentiometer_Alpha_RD901F-40-00D_Single_Vertical
RV2: 100k Scale; Potentiometer_Alpha_RD901F-40-00D_Single_Vertical
U1: LM358; DIP-8_W7.62mm_Socket_LongPads

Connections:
+5V: A1.27, C2.1, J2.11, J2.12, J5.5
+12V: C1.1, C6.1, J2.9, J2.10, U1.8
-12V: J2.1, J2.2
/5V_PCB_B: J4.5, RV1.1, RV2.1
/CV_IN: A1.19, D1.1
/CV_IN_PCB_A: D1.2, J5.6, R1.2
/CV_IN_PCB_B: C3.1, J1.T, J4.6
/GND_PCB_B: C3.2, C4.2, C5.2, J1.S, J3.S, J4.1, RV1.3, RV2.3
/LED_A: J6.2, R3.1
/LED_A_PCB_B: D2.1, D5.2, D8.1, D9.2, D12.1, D13.2, J7.2
/LED_B: J6.3, R4.1
/LED_B_PCB_B: D2.2, D3.1, D5.1, D6.2, D10.1, D11.2, J7.3
/LED_C: J6.4, R5.1
/LED_C_PCB_B: D3.2, D4.1, D6.1, D7.2, D8.2, D9.1, J7.4
/LED_D: J6.5, R6.1
/LED_D_PCB_B: D4.2, D7.1, D10.2, D11.1, D12.2, D13.1, J7.5
/NOTE_SELECT: A1.21, J6.7
/NOTE_SELECT_PCB_B: C5.1, J7.7, RV1.2
/QUANT_OUT: A1.12, R2.2
/Q_OUT_PCB_A: J5.7, U1.1, U1.2
/Q_OUT_PCB_B: J3.T, J4.7
/SCALE_SELECT: A1.22, J6.6
/SCALE_SELECT_PCB_B: C4.1, J7.6, RV2.2
GND: A1.29, C1.2, C2.2, C6.2, C7.2, J2.3, J2.4, J2.5, J2.6, J2.7, J2.8, J5.1, R1.1, U1.4
unnamed: A1.5, R3.2
unnamed: A1.6, R4.2
unnamed: A1.7, R5.2
unnamed: A1.8, R6.2
unnamed: C7.1, R2.1, U1.3
